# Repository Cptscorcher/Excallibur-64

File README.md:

# Excallibur-64
A reimagining of the seminal Excalibur 64 Computer
This is version 3 - yet to be tested but fixed a few things from version 2. Currently there are still some components that rely on 3rd party libraries and don't need to be, so in the process of removing them to make it more portable. 
There is no video yet, that is a separate beast. 

Goal for this project
=====================
Design build a new version of the  Excalibur 64. First major goal is to get all but the video going. So need to write firmware to take input from the keyboard output text via the serial port. 
Final version will have video as per original design.

Design requirements
==================
1. Needs to have the same look and feel of a real Excalibur 64. So the circuit for the sound and, parallel and keyboard is the same but with CMOS where possible.
2. Same goes for the video but need to think about a work around for the 6331-1 PROM.
3. There are some differences for practically and cost. For example using a single SRAM and single Flash ROM instead of two ROMs. Burning ROMs is a pain maybe when I do a 'pitch perfect' PCB I'll use DRAM and PROMS. The power supply is also different. At $25 I'm not using a LM323 for a +5 reg and since we are using a RS232 line driver IC there is no need for -12v. The reset circuit is different, that was simply because I don't understand how the original reset circuit worked. Its great to be authentic but a different power circuit isn't going to change the experience.

Future plans
============
1. Build a Disk Drive controller based on the WD2793 as per the original.
2. Build a HI-RES board.
3. Build some of the other board featured in the Excalibur 64 users group.
4. All the parts used on the original are still available so would be great to build one as the founders intended. All hail the founders!!

Credits
=======
All the original schematics + more is available from https://www.microbee-mspp.org/repository/ . Info from here was what this design is based on.

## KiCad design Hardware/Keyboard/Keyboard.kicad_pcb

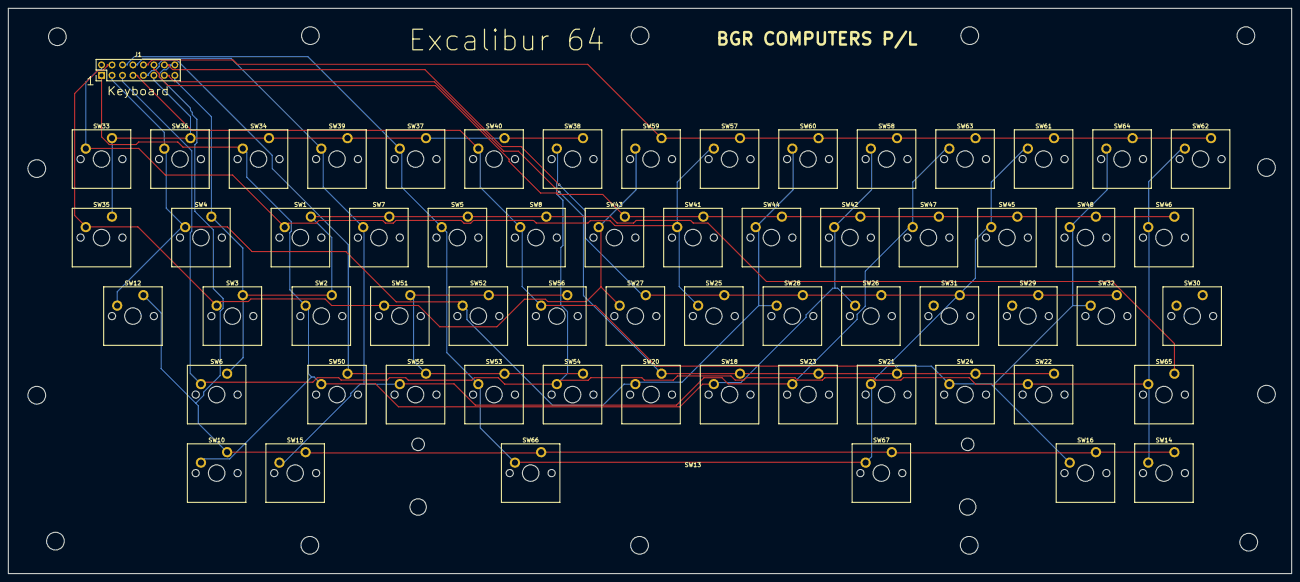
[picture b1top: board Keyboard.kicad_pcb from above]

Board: 2 copper layers, 311.4 x 137.2 mm, 77 parts (0 on the bottom side), 16 nets.

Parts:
J1: Keyboard; PinHeader_2x08_P2.54mm_Vertical
REF01, REF02, REF03, REF04, REF05, REF06, REF07, REF08, REF09, REF10, REF11, REF12, REF13, REF14: MountingHole_4.3mm_M4
SW1: Q; SW_Cherry_MX_PCB_1.00u
SW2: A; SW_Cherry_MX_PCB_1.00u
SW3: CAPSLOCK; SW_Cherry_MX_PCB_1.25u
SW4: <TAB>; SW_Cherry_MX_PCB_1.50u
SW5: E; SW_Cherry_MX_PCB_1.00u
SW6, SW65: SHIFT; SW_Cherry_MX_PCB_2.00u
SW7: W; SW_Cherry_MX_PCB_1.00u
SW8: R; SW_Cherry_MX_PCB_1.00u
SW10: F1; SW_Cherry_MX_PCB_1.00u
SW12: <CTRL>; SW_Cherry_MX_PCB_1.25u
SW13: <SPC>; Stabilizer_Cherry_MX_8.00u
SW14: F4; SW_Cherry_MX_PCB_1.00u
SW15: F2; SW_Cherry_MX_PCB_1.00u
SW16: F3; SW_Cherry_MX_PCB_1.00u
SW18: N; SW_Cherry_MX_PCB_1.00u
SW20: B; SW_Cherry_MX_PCB_1.00u
SW21: , <; SW_Cherry_MX_PCB_1.00u
SW22: / ?; SW_Cherry_MX_PCB_1.00u
SW23: M; SW_Cherry_MX_PCB_1.00u
SW24: . >; SW_Cherry_MX_PCB_1.00u
SW25: H; SW_Cherry_MX_PCB_1.00u
SW26: K; SW_Cherry_MX_PCB_1.00u
SW27: G; SW_Cherry_MX_PCB_1.00u
SW28: J; SW_Cherry_MX_PCB_1.00u
SW29: ; :; SW_Cherry_MX_PCB_1.00u
SW30: <RET>; SW_Cherry_MX_PCB_1.00u
SW31: L; SW_Cherry_MX_PCB_1.00u
SW32: ' "; SW_Cherry_MX_PCB_1.00u
SW33: LINE_INS; SW_Cherry_MX_PCB_1.00u
SW34: 1 !; SW_Cherry_MX_PCB_1.00u
SW35: <ESC>; SW_Cherry_MX_PCB_1.00u
SW36: LINE_DEL; SW_Cherry_MX_PCB_1.00u
SW37: 3 #; SW_Cherry_MX_PCB_1.00u
SW38: 5 %; SW_Cherry_MX_PCB_1.00u
SW39: 2 @; SW_Cherry_MX_PCB_1.00u
SW40: 4 $; SW_Cherry_MX_PCB_1.00u
SW41: Y; SW_Cherry_MX_PCB_1.00u
SW42: I; SW_Cherry_MX_PCB_1.00u
SW43: T; SW_Cherry_MX_PCB_1.00u
SW44: U; SW_Cherry_MX_PCB_1.00u
SW45: P; SW_Cherry_MX_PCB_1.00u
SW46: ] }; SW_Cherry_MX_PCB_1.00u
SW47: O; SW_Cherry_MX_PCB_1.00u
SW48: [ {; SW_Cherry_MX_PCB_1.00u
SW50: Z; SW_Cherry_MX_PCB_1.00u
SW51: S; SW_Cherry_MX_PCB_1.00u
SW52: D; SW_Cherry_MX_PCB_1.00u
SW53: C; SW_Cherry_MX_PCB_1.00u
SW54: V; SW_Cherry_MX_PCB_1.00u
SW55: X; SW_Cherry_MX_PCB_1.00u
SW56: F; SW_Cherry_MX_PCB_1.00u
SW57: 7 &; SW_Cherry_MX_PCB_1.00u
SW58: 9 (; SW_Cherry_MX_PCB_1.00u
SW59: 6 ^; SW_Cherry_MX_PCB_1.00u
SW60: 8 *; SW_Cherry_MX_PCB_1.00u
SW61: - _; SW_Cherry_MX_PCB_1.00u
SW62: <BKSP>; SW_Cherry_MX_PCB_1.00u
SW63: 0 ); SW_Cherry_MX_PCB_1.00u
SW64: = +; SW_Cherry_MX_PCB_1.00u
SW66, SW67: <SPC>; SW_Cherry_MX_PCB_1.00u

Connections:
COL0: J1.7, SW8.1, SW16.1, SW24.1, SW32.1, SW40.1, SW48.1, SW56.1, SW64.1
COL1: J1.8, SW7.1, SW15.1, SW23.1, SW31.1, SW39.1, SW47.1, SW55.1, SW63.1
COL2: J1.5, SW6.1, SW14.1, SW22.1, SW30.1, SW38.1, SW46.1, SW54.1, SW62.1, SW65.1
COL3: J1.6, SW5.1, SW21.1, SW29.1, SW37.1, SW45.1, SW53.1, SW61.1, SW66.1, SW67.1
COL4: J1.3, SW4.1, SW12.1, SW20.1, SW28.1, SW36.1, SW44.1, SW52.1, SW60.1
COL5: J1.4, SW3.1, SW27.1, SW35.1, SW43.1, SW51.1, SW59.1
COL6: J1.1, SW2.1, SW10.1, SW18.1, SW26.1, SW34.1, SW42.1, SW50.1, SW58.1
COL7: J1.2, SW1.1, SW25.1, SW33.1, SW41.1, SW57.1
ROW0: J1.10, SW57.2, SW58.2, SW59.2, SW60.2, SW61.2, SW62.2, SW63.2, SW64.2
ROW1: J1.9, SW50.2, SW51.2, SW52.2, SW53.2, SW54.2, SW55.2, SW56.2
ROW2: J1.12, SW41.2, SW42.2, SW43.2, SW44.2, SW45.2, SW46.2, SW47.2, SW48.2
ROW3: J1.11, SW33.2, SW34.2, SW35.2, SW36.2, SW37.2, SW38.2, SW39.2, SW40.2
ROW4: J1.14, SW25.2, SW26.2, SW27.2, SW28.2, SW29.2, SW30.2, SW31.2, SW32.2
ROW5: J1.13, SW18.2, SW20.2, SW21.2, SW22.2, SW23.2, SW24.2
ROW6: J1.16, SW10.2, SW12.2, SW14.2, SW15.2, SW16.2, SW66.2, SW67.2
ROW7: J1.15, SW1.2, SW2.2, SW3.2, SW4.2, SW5.2, SW6.2, SW7.2, SW8.2, SW65.2

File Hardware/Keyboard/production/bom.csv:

Designator,Footprint,Quantity,Value,LCSC Part #
J1,PinHeader_2x08_P2.54mm_Vertical,1,Keyboard,
SW1,SW_Cherry_MX_PCB_1.00u,1,Q,
SW10,SW_Cherry_MX_PCB_1.00u,1,F1,
SW12,SW_Cherry_MX_PCB_1.25u,1,<CTRL>,
SW13,Stabilizer_Cherry_MX_8.00u,1,<SPC>,
SW14,SW_Cherry_MX_PCB_1.00u,1,F4,
SW15,SW_Cherry_MX_PCB_1.00u,1,F2,
SW16,SW_Cherry_MX_PCB_1.00u,1,F3,
SW18,SW_Cherry_MX_PCB_1.00u,1,N,
SW2,SW_Cherry_MX_PCB_1.00u,1,A,
SW20,SW_Cherry_MX_PCB_1.00u,1,B,
SW21,SW_Cherry_MX_PCB_1.00u,1,", <",
SW22,SW_Cherry_MX_PCB_1.00u,1,/ ?,
SW23,SW_Cherry_MX_PCB_1.00u,1,M,
SW24,SW_Cherry_MX_PCB_1.00u,1,. >,
SW25,SW_Cherry_MX_PCB_1.00u,1,H,
SW26,SW_Cherry_MX_PCB_1.00u,1,K,
SW27,SW_Cherry_MX_PCB_1.00u,1,G,
SW28,SW_Cherry_MX_PCB_1.00u,1,J,
SW29,SW_Cherry_MX_PCB_1.00u,1,; :,
SW3,SW_Cherry_MX_PCB_1.25u,1,CAPSLOCK,
SW30,SW_Cherry_MX_PCB_1.00u,1,<RET>,
SW31,SW_Cherry_MX_PCB_1.00u,1,L,
SW32,SW_Cherry_MX_PCB_1.00u,1,"' """,
SW33,SW_Cherry_MX_PCB_1.00u,1,LINE_INS,
SW34,SW_Cherry_MX_PCB_1.00u,1,1 !,
SW35,SW_Cherry_MX_PCB_1.00u,1,<ESC>,
SW36,SW_Cherry_MX_PCB_1.00u,1,LINE_DEL,
SW37,SW_Cherry_MX_PCB_1.00u,1,3 #,
SW38,SW_Cherry_MX_PCB_1.00u,1,5 %,
SW39,SW_Cherry_MX_PCB_1.00u,1,2 @,
SW4,SW_Cherry_MX_PCB_1.50u,1,<TAB>,
SW40,SW_Cherry_MX_PCB_1.00u,1,4 $,
SW41,SW_Cherry_MX_PCB_1.00u,1,Y,
SW42,SW_Cherry_MX_PCB_1.00u,1,I,
SW43,SW_Cherry_MX_PCB_1.00u,1,T,
SW44,SW_Cherry_MX_PCB_1.00u,1,U,
SW45,SW_Cherry_MX_PCB_1.00u,1,P,
SW46,SW_Cherry_MX_PCB_1.00u,1,] },
SW47,SW_Cherry_MX_PCB_1.00u,1,O,
SW48,SW_Cherry_MX_PCB_1.00u,1,[ {,
SW5,SW_Cherry_MX_PCB_1.00u,1,E,
SW50,SW_Cherry_MX_PCB_1.00u,1,Z,
SW51,SW_Cherry_MX_PCB_1.00u,1,S,
SW52,SW_Cherry_MX_PCB_1.00u,1,D,
SW53,SW_Cherry_MX_PCB_1.00u,1,C,
SW54,SW_Cherry_MX_PCB_1.00u,1,V,
SW55,SW_Cherry_MX_PCB_1.00u,1,X,
SW56,SW_Cherry_MX_PCB_1.00u,1,F,
SW57,SW_Cherry_MX_PCB_1.00u,1,7 &,
SW58,SW_Cherry_MX_PCB_1.00u,1,9 (,
SW59,SW_Cherry_MX_PCB_1.00u,1,6 ^,
"SW6, SW65",SW_Cherry_MX_PCB_2.00u,2,SHIFT,
SW60,SW_Cherry_MX_PCB_1.00u,1,8 *,
SW61,SW_Cherry_MX_PCB_1.00u,1,- _,
SW62,SW_Cherry_MX_PCB_1.00u,1,<BKSP>,
SW63,SW_Cherry_MX_PCB_1.00u,1,0 ),
SW64,SW_Cherry_MX_PCB_1.00u,1,= +,
"SW66, SW67",SW_Cherry_MX_PCB_1.00u,2,<SPC>,
SW7,SW_Cherry_MX_PCB_1.00u,1,W,
SW8,SW_Cherry_MX_PCB_1.00u,1,R,

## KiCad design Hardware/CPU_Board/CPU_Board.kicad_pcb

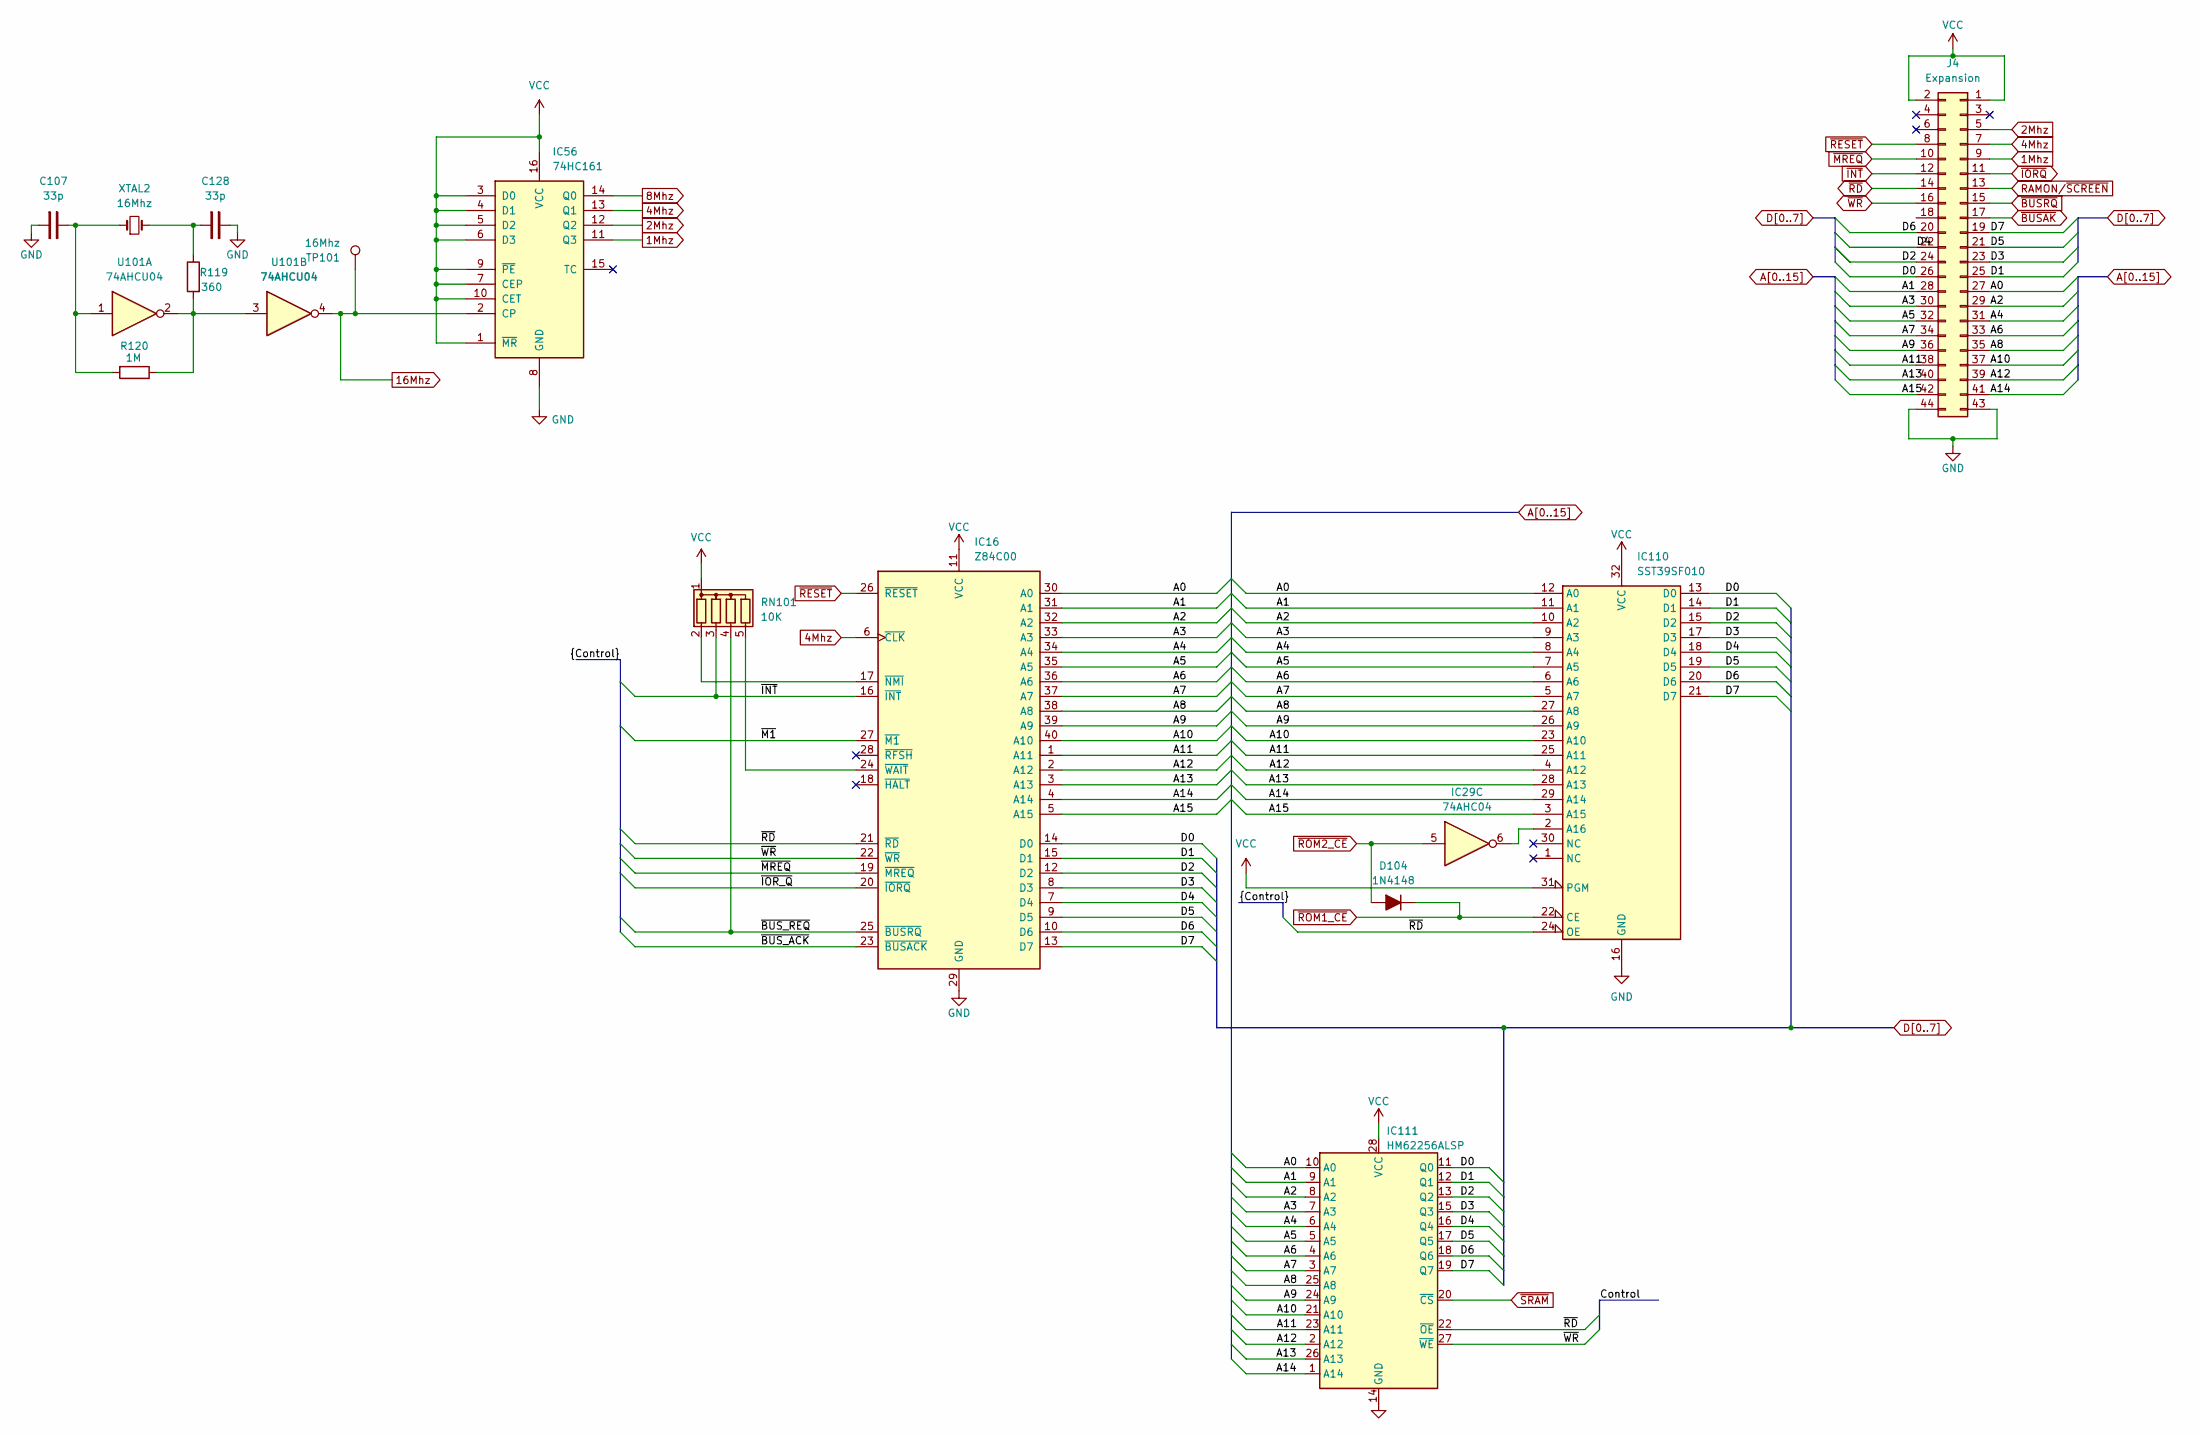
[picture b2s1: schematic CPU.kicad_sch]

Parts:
C107, C128: 33p; C_Disc_D3.0mm_W2.0mm_P2.50mm
D104: 1N4148; D_DO-35_SOD27_P7.62mm_Horizontal
IC16: Z84C00; DIP-40_W15.24mm_LongPads
IC29: 74AHC04; DIP-14_W7.62mm_Socket_LongPads
IC56: 74HC161; DIP-16_W7.62mm_Socket_LongPads
IC110: SST39SF010; DIP_Socket-32_W11.9_W12.7_W15.24_W17.78_W18.5_3M_232-1285-0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
IC111: HM62256ALSP; DIP-28_W15.24mm_Socket_LongPads
J4: Expansion; PinHeader_2x22_P2.54mm_Vertical
R119: 360; R_Axial_DIN0207_L6.3mm_D2.5mm_P10.16mm_Horizontal
R120: 1M; R_Axial_DIN0207_L6.3mm_D2.5mm_P10.16mm_Horizontal
RN101: 10K; R_Array_SIP5
TP101: 16Mhz; TestPoint_Loop_D1.80mm_Drill1.0mm_Beaded
U101: 74AHCU04; DIP-14_W7.62mm_Socket_LongPads
XTAL2: 16Mhz; Crystal_HC49-U_Vertical

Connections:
1Mhz: IC56.11 (Q3), J4.9
2Mhz: IC56.12 (Q2), J4.5; also elsewhere on the board
4Mhz: IC16.6 (~CLK), IC56.13 (Q1), J4.7
8Mhz: IC56.14 (Q0)
/CPU/~BUS_ACK: IC16.23 (~BUSACK)
/CPU/~BUS_REQ: IC16.25 (~BUSRQ), RN101.4 (R3)
/CPU/~IOR_Q: IC16.20 (~IORQ)
/CPU/~M1: IC16.27 (~M1)
A0: IC16.30 (A0), IC110.12 (A0), IC111.10 (A0), J4.27; also elsewhere on the board
A1: IC16.31 (A1), IC110.11 (A1), IC111.9 (A1), J4.28; also elsewhere on the board
A2: IC16.32 (A2), IC110.10 (A2), IC111.8 (A2), J4.29
A3: IC16.33 (A3), IC110.9 (A3), IC111.7 (A3), J4.30
A4: IC16.34 (A4), IC110.8 (A4), IC111.6 (A4), J4.31; also elsewhere on the board
A5: IC16.35 (A5), IC110.7 (A5), IC111.5 (A5), J4.32; also elsewhere on the board
A6: IC16.36 (A6), IC110.6 (A6), IC111.4 (A6), J4.33; also elsewhere on the board
A7: IC16.37 (A7), IC110.5 (A7), IC111.3 (A7), J4.34; also elsewhere on the board
A8: IC16.38 (A8), IC110.27 (A8), IC111.25 (A8), J4.35
A9: IC16.39 (A9), IC110.26 (A9), IC111.24 (A9), J4.36
A10: IC16.40 (A10), IC110.23 (A10), IC111.21 (A10), J4.37
A11: IC16.1 (A11), IC110.25 (A11), IC111.23 (A11), J4.38; also elsewhere on the board
A12: IC16.2 (A12), IC110.4 (A12), IC111.2 (A12), J4.39; also elsewhere on the board
A13: IC16.3 (A13), IC110.28 (A13), IC111.26 (A13), J4.40; also elsewhere on the board
A14: IC16.4 (A14), IC110.29 (A14), IC111.1 (A14), J4.41
A15: IC16.5 (A15), IC110.3 (A15), J4.42; also elsewhere on the board
D0: IC16.14 (D0), IC110.13 (D0), IC111.11 (Q0), J4.26; also elsewhere on the board
D1: IC16.15 (D1), IC110.14 (D1), IC111.12 (Q1), J4.25; also elsewhere on the board
D2: IC16.12 (D2), IC110.15 (D2), IC111.13 (Q2), J4.24; also elsewhere on the board
D3: IC16.8 (D3), IC110.17 (D3), IC111.15 (Q3), J4.23; also elsewhere on the board
D4: IC16.7 (D4), IC110.18 (D4), IC111.16 (Q4), J4.22; also elsewhere on the board
D5: IC16.9 (D5), IC110.19 (D5), IC111.17 (Q5), J4.21; also elsewhere on the board
D6: IC16.10 (D6), IC110.20 (D6), IC111.18 (Q6), J4.20; also elsewhere on the board
D7: IC16.13 (D7), IC110.21 (D7), IC111.19 (Q7), J4.19; also elsewhere on the board
unnamed: C128.1, R119.1, XTAL2.2
unnamed: IC16.17 (~NMI), RN101.2 (R1)
unnamed: IC16.24 (~WAIT), RN101.5 (R4)
unnamed: IC29.6, IC110.2 (A16)
RAMON/~SCREEN: J4.13; also elsewhere on the board
VCC: IC16.11 (VCC), IC56.1 (~MR), IC56.3 (D0), IC56.4 (D1), IC56.5 (D2), IC56.6 (D3), IC56.7 (CEP), IC56.9 (~PE), IC56.10 (CET), IC56.16 (VCC), IC110.31 (PGM), IC110.32 (VCC), IC111.28 (VCC), J4.1, J4.2, RN101.1 (common); also elsewhere on the board
~BUSAK: J4.17
~BUSRQ: J4.15
~INT: IC16.16 (~INT), J4.12, RN101.3 (R2)
~IORQ: J4.11
~MREQ: IC16.19 (~MREQ), J4.10
~RD: IC16.21 (~RD), IC110.24 (OE), IC111.22 (~OE), J4.14; also elsewhere on the board
~RESET: IC16.26 (~RESET), J4.8
~ROM1_CE: D104.1 (K), IC110.22 (CE); also elsewhere on the board
~ROM2_CE: D104.2 (A), IC29.5; also elsewhere on the board
~SRAM: IC111.20 (~CS); also elsewhere on the board
~WR: IC16.22 (~WR), IC111.27 (~WE), J4.16; also elsewhere on the board

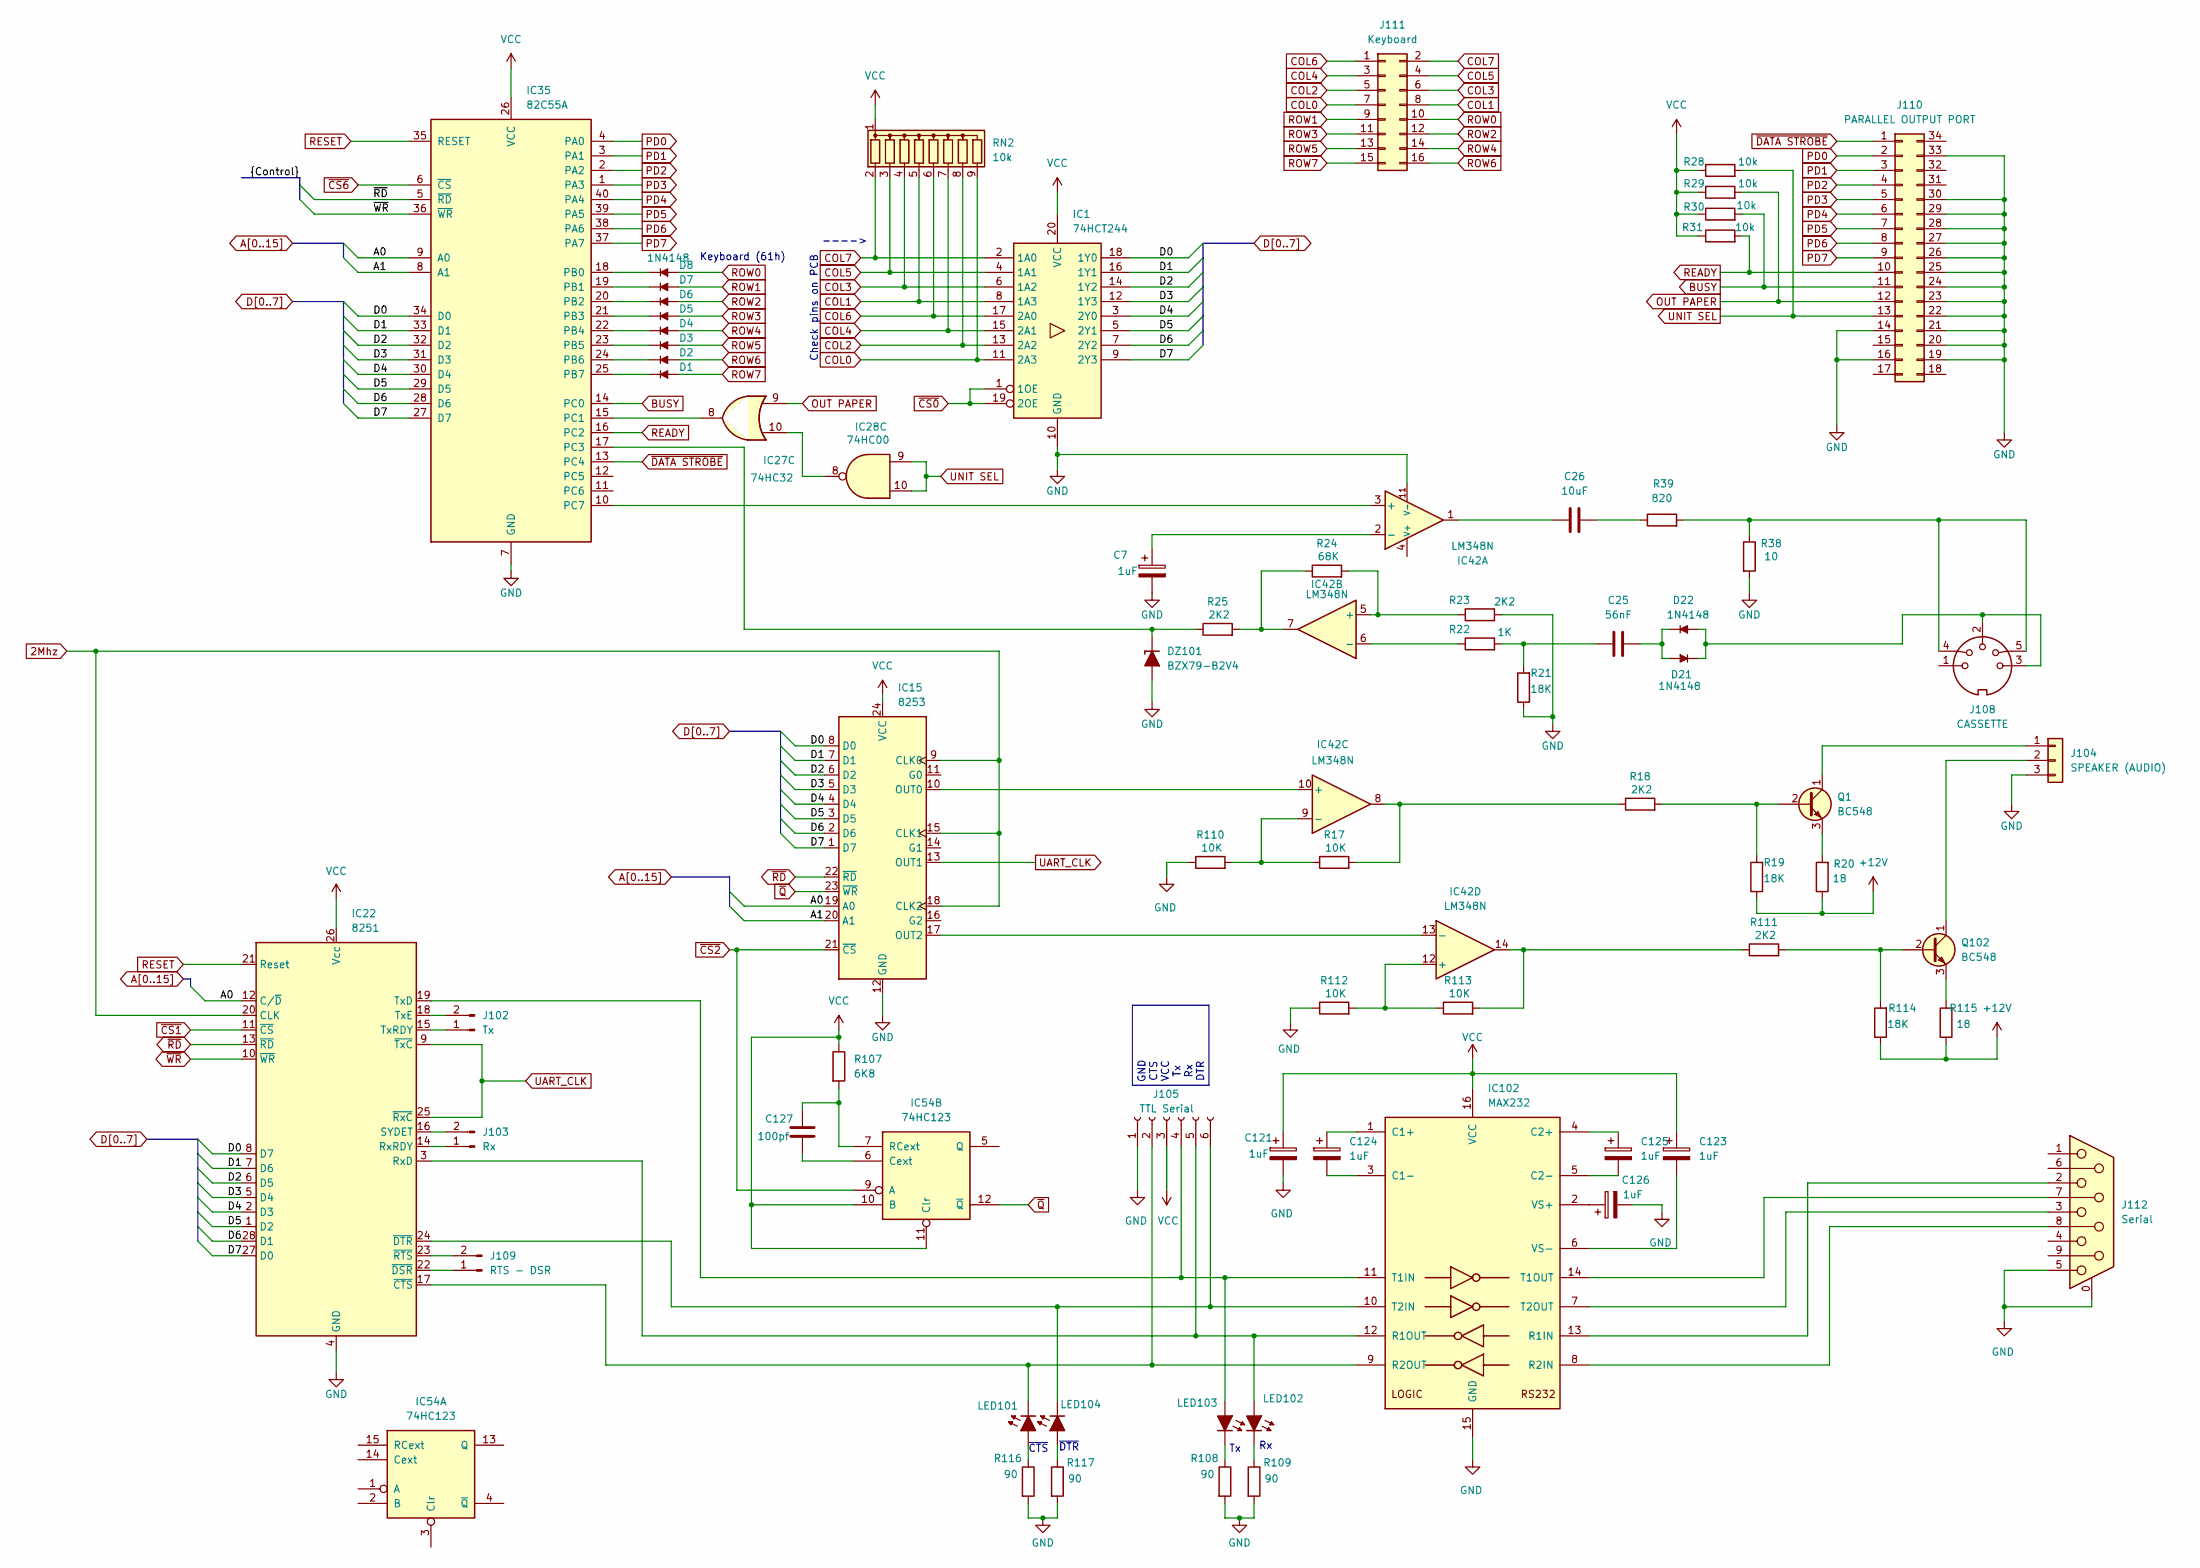
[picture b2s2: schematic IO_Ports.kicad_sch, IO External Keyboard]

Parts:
C7, C121, C123, C124, C125, C126: 1uF; CP_Radial_D6.3mm_P2.50mm
C25: 56nF; C_Disc_D3.4mm_W2.1mm_P2.50mm
C26: 10uF; C_Radial_D6.3mm_H5.0mm_P2.50mm
C127: 100pf; C_Disc_D3.8mm_W2.6mm_P2.50mm
D1, D2, D3, D4, D5, D6, D7, D8, D21, D22: 1N4148; D_A-405_P7.62mm_Horizontal
DZ101: BZX79-B2V4; D_DO-35_SOD27_P7.62mm_Horizontal_Zener
IC1: 74HCT244; DIP-20_W7.62mm_LongPads
IC15: 8253; DIP-24_W15.24mm_LongPads
IC22: 8251; DIP-28_W15.24mm_LongPads
IC27: 74HC32; DIP-14_W7.62mm_LongPads
IC28: 74HC00; DIP-14_W7.62mm_LongPads
IC35: 82C55A; DIP-40_W15.24mm_LongPads
IC42: LM348N; DIP-14_W7.62mm_LongPads
IC54: 74HC123; DIP-16_W7.62mm_LongPads
IC102: MAX232; DIP-16_W7.62mm_LongPads
J102: Tx; PinHeader_1x02_P2.54mm_Vertical
J103: Rx; PinHeader_1x02_P2.54mm_Vertical
J104: SPEAKER (AUDIO); PinSocket_1x03_P2.54mm_Vertical
J105: TTL Serial; PinHeader_1x06_P2.54mm_Vertical
J108: CASSETTE; DIN_5
J109: RTS - DSR; PinHeader_1x02_P2.54mm_Vertical
J110: PARALLEL OUTPUT PORT; IDC-Header_2x17_P2.54mm_Latch_Horizontal
J111: Keyboard; PinHeader_2x08_P2.54mm_Vertical
J112: Serial; DSUB-9_Female_Horizontal_P2.77x2.84mm_EdgePinOffset4.94mm_H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
LED101, LED103: Red; LED_1206_3216Metric
LED102, LED104: Green; LED_1206_3216Metric
Q1, Q102: BC548; TO-92_Inline_Wide_CBE
R17, R110, R112, R113: 10K; R_Axial_DIN0207_L6.3mm_D2.5mm_P10.16mm_Horizontal
R18, R23, R25, R111: 2K2; R_Axial_DIN0207_L6.3mm_D2.5mm_P10.16mm_Horizontal
R19, R21, R114: 18K; R_Axial_DIN0207_L6.3mm_D2.5mm_P10.16mm_Horizontal
R20, R115: 18; R_Axial_DIN0207_L6.3mm_D2.5mm_P10.16mm_Horizontal
R22: 1K; R_Axial_DIN0207_L6.3mm_D2.5mm_P10.16mm_Horizontal
R24: 68K; R_Axial_DIN0207_L6.3mm_D2.5mm_P10.16mm_Horizontal
R28, R29, R30, R31: 10k; R_Axial_DIN0207_L6.3mm_D2.5mm_P10.16mm_Horizontal
R38: 10; R_Axial_DIN0207_L6.3mm_D2.5mm_P10.16mm_Horizontal
R39: 820; R_Axial_DIN0207_L6.3mm_D2.5mm_P10.16mm_Horizontal
R107: 6K8; R_Axial_DIN0207_L6.3mm_D2.5mm_P7.62mm_Horizontal
R108, R109, R116, R117: 90; R_1206_3216Metric_Pad1.30x1.75mm_HandSolder
RN2: 10k; R_Array_SIP9

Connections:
2Mhz: IC15.9 (CLK0), IC15.15 (CLK1), IC15.18 (CLK2), IC22.20 (CLK); also elsewhere on the board
+12V: R19.1, R20.1, R114.1, R115.1; also elsewhere on the board
A0: IC15.19 (A0), IC22.12 (C/~D), IC35.9 (A0); also elsewhere on the board
A1: IC15.20 (A1), IC35.8 (A1); also elsewhere on the board
BUSY: IC35.14 (PC0), J110.11, R30.2
COL0: IC1.11 (2A3), J111.7, RN2.9 (R8)
COL1: IC1.8 (1A3), J111.8, RN2.5 (R4)
COL2: IC1.13 (2A2), J111.5, RN2.8 (R7)
COL3: IC1.6 (1A2), J111.6, RN2.4 (R3)
COL4: IC1.15 (2A1), J111.3, RN2.7 (R6)
COL5: IC1.4 (1A1), J111.4, RN2.3 (R2)
COL6: IC1.17 (2A0), J111.1, RN2.6 (R5)
COL7: IC1.2 (1A0), J111.2, RN2.2 (R1)
D0: IC1.18 (1Y0), IC15.8 (D0), IC22.8 (D7), IC35.34 (D0); also elsewhere on the board
D1: IC1.16 (1Y1), IC15.7 (D1), IC22.7 (D6), IC35.33 (D1); also elsewhere on the board
D2: IC1.14 (1Y2), IC15.6 (D2), IC22.6 (D5), IC35.32 (D2); also elsewhere on the board
D3: IC1.12 (1Y3), IC15.5 (D3), IC22.5 (D4), IC35.31 (D3); also elsewhere on the board
D4: IC1.3 (2Y0), IC15.4 (D4), IC22.2 (D3), IC35.30 (D4); also elsewhere on the board
D5: IC1.5 (2Y1), IC15.3 (D5), IC22.1 (D2), IC35.29 (D5); also elsewhere on the board
D6: IC1.7 (2Y2), IC15.2 (D6), IC22.28 (D1), IC35.28 (D6); also elsewhere on the board
D7: IC1.9 (2Y3), IC15.1 (D7), IC22.27 (D0), IC35.27 (D7); also elsewhere on the board
unnamed: C25.1, R21.2, R22.2
unnamed: C25.2, D21.1, D22.2
unnamed: C26.1, IC42.1
unnamed: C26.2, R39.1
unnamed: D21.2, D22.1, J108.2, J108.3
unnamed: DZ101.1 (K), IC35.17 (PC3), R25.1
unnamed: IC15.10 (OUT0), IC42.10 (+)
unnamed: IC15.17 (OUT2), IC42.13 (-)
unnamed: IC22.14 (RxRDY), J103.1
unnamed: IC22.16 (SYDET), J103.2
unnamed: IC22.18 (TxE), J102.2
unnamed: IC22.15 (TxRDY), J102.1
unnamed: IC22.22 (~DSR), J109.1
unnamed: IC22.23 (~RTS), J109.2
unnamed: IC27.10, IC28.8
unnamed: D8.2, IC35.18 (PB0)
unnamed: D7.2, IC35.19 (PB1)
unnamed: D6.2, IC35.20 (PB2)
unnamed: D5.2, IC35.21 (PB3)
unnamed: D4.2, IC35.22 (PB4)
unnamed: D3.2, IC35.23 (PB5)
unnamed: D2.2, IC35.24 (PB6)
unnamed: D1.2, IC35.25 (PB7)
unnamed: IC27.8, IC35.15 (PC1)
unnamed: IC35.10 (PC7), IC42.3 (+)
unnamed: IC42.7, R24.1, R25.2
unnamed: IC42.8, R17.2, R18.1
unnamed: IC42.14, R111.1, R113.2
unnamed: C7.1, IC42.2 (-)
unnamed: IC42.5 (+), R23.1, R24.2
unnamed: IC42.6 (-), R22.1
unnamed: IC42.9 (-), R17.1, R110.2
unnamed: IC42.12 (+), R112.2, R113.1
unnamed: C127.1, IC54.6 (Cext)
unnamed: C127.2, IC54.7 (RCext), R107.2
unnamed: C124.1, IC102.1 (C1+)
unnamed: C124.2, IC102.3 (C1-)
unnamed: C125.1, IC102.4 (C2+)
unnamed: C125.2, IC102.5 (C2-)
unnamed: IC102.13 (R1IN), J112.2
unnamed: IC22.3 (RxD), IC102.12 (R1OUT), J105.5, LED102.2 (A)
unnamed: IC102.8 (R2IN), J112.8
unnamed: IC22.17 (~CTS), IC102.9 (R2OUT), J105.2, LED101.1 (K)
unnamed: IC22.19 (TxD), IC102.11 (T1IN), J105.4, LED103.2 (A)
unnamed: IC102.14 (T1OUT), J112.7
unnamed: IC22.24 (~DTR), IC102.10 (T2IN), J105.6, LED104.1 (K)
unnamed: IC102.7 (T2OUT), J112.3
unnamed: C126.1, IC102.2 (VS+)
unnamed: C123.2, IC102.6 (VS-)
unnamed: J104.1, Q1.1 (C)
unnamed: J104.2, Q102.1 (C)
unnamed: J108.4, J108.5, R38.1, R39.2
unnamed: LED101.2 (A), R116.1
unnamed: LED102.1 (K), R109.1
unnamed: LED103.1 (K), R108.1
unnamed: LED104.2 (A), R117.1
unnamed: Q1.2 (B), R18.2, R19.2
unnamed: Q1.3 (E), R20.2
unnamed: Q102.2 (B), R111.2, R114.2
unnamed: Q102.3 (E), R115.2
OUT PAPER: IC27.9, J110.12, R29.2
PD0: IC35.4 (PA0), J110.2
PD1: IC35.3 (PA1), J110.3
PD2: IC35.2 (PA2), J110.4
PD3: IC35.1 (PA3), J110.5
PD4: IC35.40 (PA4), J110.6
PD5: IC35.39 (PA5), J110.7
PD6: IC35.38 (PA6), J110.8
PD7: IC35.37 (PA7), J110.9
READY: IC35.16 (PC2), J110.10, R31.2
RESET: IC22.21 (Reset), IC35.35 (RESET)
ROW0: D8.1, J111.10
ROW1: D7.1, J111.9
ROW2: D6.1, J111.12
ROW3: D5.1, J111.11
ROW4: D4.1, J111.14
ROW5: D3.1, J111.13
ROW6: D2.1, J111.16
ROW7: D1.1, J111.15
UART_CLK: IC15.13 (OUT1), IC22.9 (~TxC), IC22.25 (~RxC)
UNIT SEL: IC28.9, IC28.10, J110.13, R28.2
VCC: C121.1, C123.1, IC1.20 (VCC), IC15.24 (VCC), IC22.26 (Vcc), IC35.26 (VCC), IC54.10 (B), IC54.11 (Clr), IC102.16 (VCC), J105.3, R28.1, R29.1, R30.1, R31.1, R107.1, RN2.1 (common); also elsewhere on the board
~CS0: IC1.1 (1OE), IC1.19 (2OE); also elsewhere on the board
~CS1: IC22.11 (~CS); also elsewhere on the board
~CS2: IC15.21 (~CS), IC54.9 (A); also elsewhere on the board
~CS6: IC35.6 (~CS); also elsewhere on the board
~DATA STROBE: IC35.13 (PC4), J110.1
~Q: IC15.23 (~WR), IC54.12 (~Q)
~RD: IC15.22 (~RD), IC22.13 (~RD), IC35.5 (~RD); also elsewhere on the board
~WR: IC22.10 (~WR), IC35.36 (~WR); also elsewhere on the board

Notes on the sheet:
Check pins on PCB
~{DTR}
Keyboard (61h)
---->
GND CTS VCC Tx Rx DTR
~{CTS}

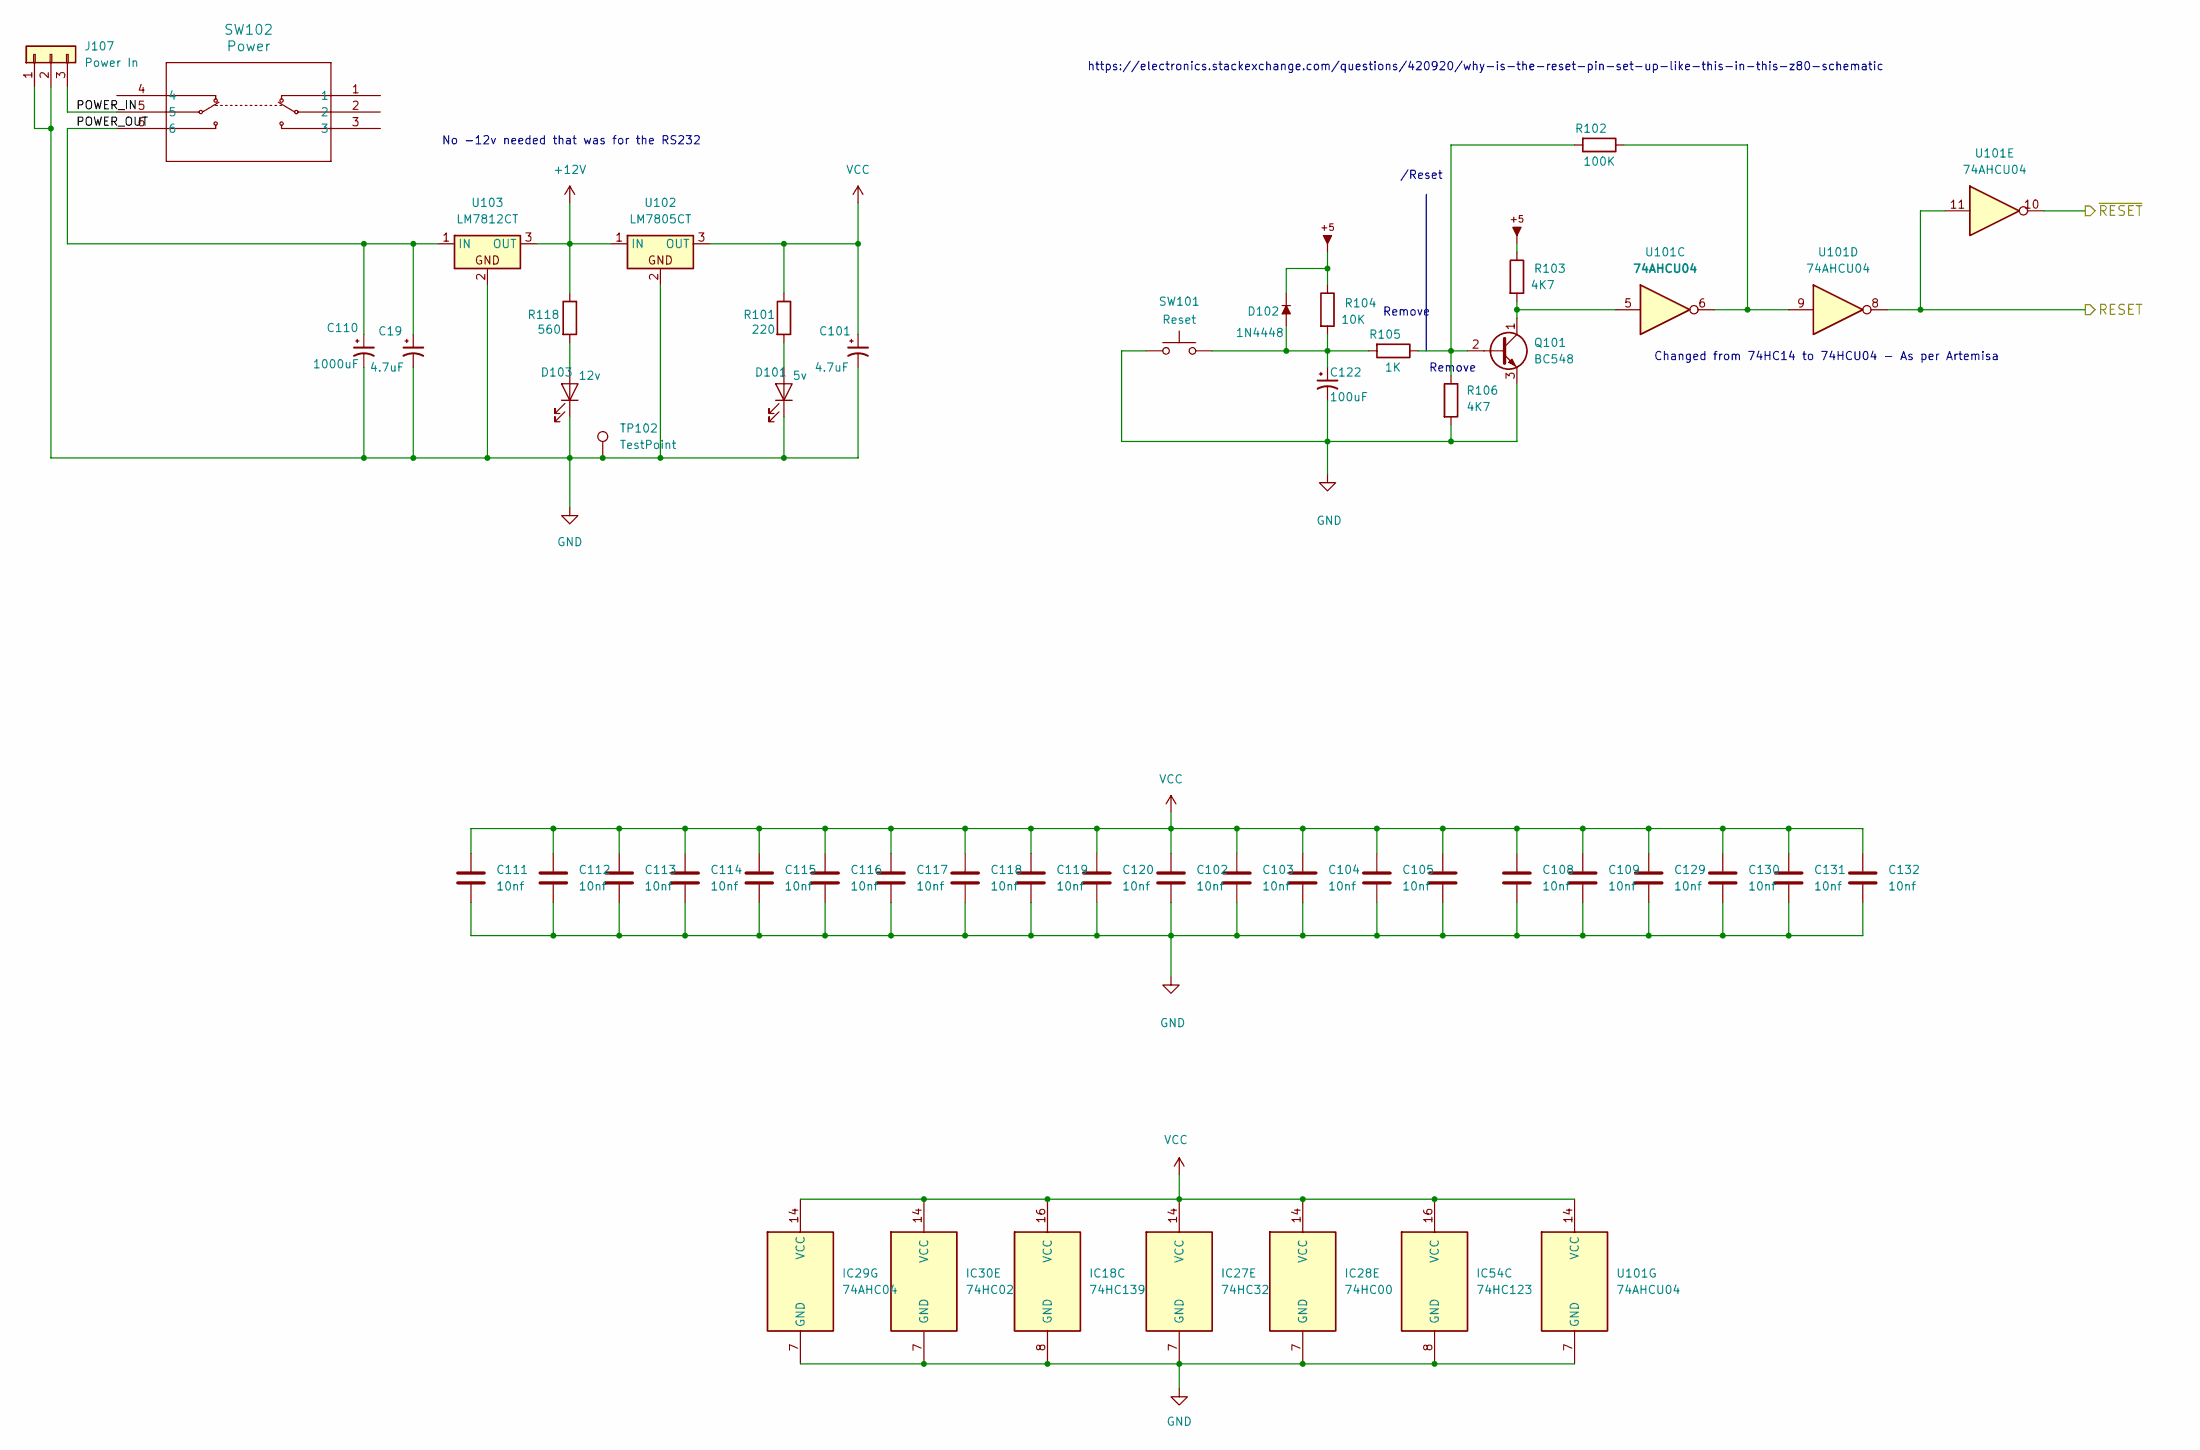
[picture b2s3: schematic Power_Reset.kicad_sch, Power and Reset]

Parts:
C19, C101: 4.7uF; CP_Radial_D6.3mm_P2.50mm
C102, C103, C104, C105, C106, C108, C109, C111, C112, C113, C114, C115, C116, C117, C118, C119, C120, C129, C130, C131, C132: 10nf; C_Disc_D3.4mm_W2.1mm_P2.50mm
C110: 1000uF; CP_Radial_D14.0mm_P5.00mm
C122: 100uF; CP_Radial_D6.3mm_P2.50mm
D101: 5v; LED_D5.0mm
D102: 1N4448; D_A-405_P7.62mm_Horizontal
D103: 12v; LED_D5.0mm
IC18: 74HC139; DIP-16_W7.62mm_Socket_LongPads
IC27: 74HC32; DIP-14_W7.62mm_LongPads
IC28: 74HC00; DIP-14_W7.62mm_LongPads
IC29: 74AHC04; DIP-14_W7.62mm_Socket_LongPads
IC30: 74HC02; DIP-14_W7.62mm_LongPads
IC54: 74HC123; DIP-16_W7.62mm_LongPads
J107: Power In; PinHeader_1x03_P2.54mm_Vertical
Q101: BC548; TO-92_Inline
R101: 220; R_Axial_DIN0207_L6.3mm_D2.5mm_P10.16mm_Horizontal
R102: 100K; R_Axial_DIN0207_L6.3mm_D2.5mm_P10.16mm_Horizontal
R103, R106: 4K7; R_Axial_DIN0207_L6.3mm_D2.5mm_P10.16mm_Horizontal
R104: 10K; R_Axial_DIN0207_L6.3mm_D2.5mm_P10.16mm_Horizontal
R105: 1K; R_Axial_DIN0207_L6.3mm_D2.5mm_P10.16mm_Horizontal
R118: 560; R_Axial_DIN0207_L6.3mm_D2.5mm_P10.16mm_Horizontal
SW101: Reset; SW_SPST_Omron_B3FS-100xP
SW102: Power; MFS201N-16-Z_NDC
TP102: TestPoint; TestPoint_Plated_Hole_D2.0mm
U101: 74AHCU04; DIP-14_W7.62mm_Socket_LongPads
U102: LM7805CT; TO-220-3_Vertical
U103: LM7812CT; TO-220-3_Vertical

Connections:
+12V: R118.1, U102.1 (IN), U103.3 (OUT); also elsewhere on the board
/Power_Reset/POWER_IN: J107.3, SW102.5
/Power_Reset/POWER_OUT: C19.1, C110.1, SW102.6, U103.1 (IN)
/Power_Reset/~RESET: U101.8, U101.11; also elsewhere on the board
unnamed: C122.1, D102.1, R104.2, R105.2, SW101.2
unnamed: D101.1 (A), R101.2
unnamed: D103.1 (A), R118.2
unnamed: Q101.2 (B), R102.2, R105.1, R106.1
VCC: C101.1, C102.1, C103.1, C104.1, C105.1, C106.1, C108.1, C109.1, C111.1, C112.1, C113.1, C114.1, C115.1, C116.1, C117.1, C118.1, C119.1, C120.1, C129.1, C130.1, C131.1, C132.1, D102.2, IC18.16 (VCC), IC27.14 (VCC), IC28.14 (VCC), IC29.14 (VCC), IC30.14 (VCC), IC54.16 (VCC), R101.1, R103.1, R104.1, U101.14 (VCC), U102.3 (OUT); also elsewhere on the board

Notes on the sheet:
https://electronics.stackexchange.com/questions/420920/why-is-the-reset-pin-set-up-like-this-in-this-z80-schematic
Changed from 74HC14 to 74HCU04 - As per Artemisa
Remove
No -12v needed that was for the RS232
/Reset
